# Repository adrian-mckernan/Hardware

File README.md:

# Hardware
PCB design files for LTC6946 based PLL array

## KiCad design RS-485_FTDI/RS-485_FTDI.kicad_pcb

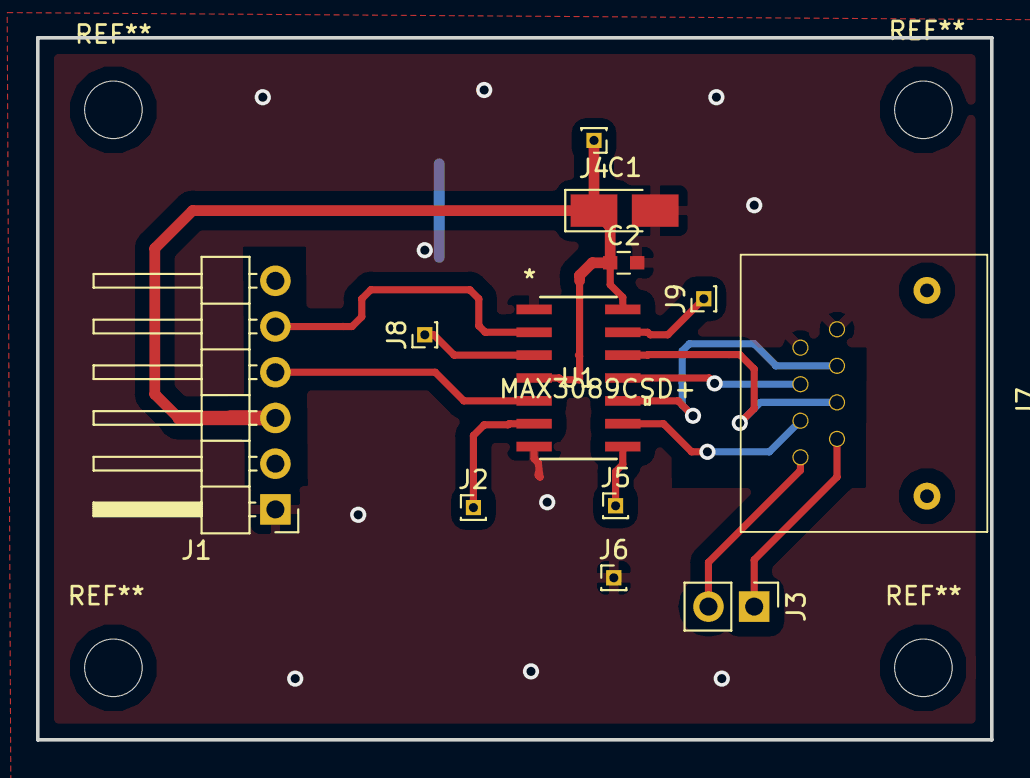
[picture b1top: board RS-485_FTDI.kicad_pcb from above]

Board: 2 copper layers, 53.0 x 39.0 mm, 12 parts (0 on the bottom side), 14 nets.

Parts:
C1: 10U; CP_Tantalum_Case-R_EIA-2012-12_Hand
C2: C; C_0603
J1: Conn_01x06; Pin_Header_Angled_1x06_Pitch2.54mm
J2, J4, J5, J6, J8, J9: Conn_01x01; Pin_Header_Straight_1x01_Pitch1.00mm
J3: Conn_01x02; Pin_Header_Straight_1x02_Pitch2.54mm
J7: RJ45; RJ-45_1572189
U1: MAX3089CSD+; MAX3089CSD&plus_

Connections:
+5V: C1.1, C2.1, J1.3, J4.1, U1.4, U1.14
GND: C1.2, C2.2, J1.1, J6.1, J7.1, J7.2, U1.1, U1.7
unnamed: J2.1, U1.6
unnamed: J3.1, J7.8
unnamed: J3.2, J7.7
unnamed: J5.1, U1.8
unnamed: J8.1, U1.3
unnamed: J9.1, U1.13
RXI: J1.5, U1.2
TXO: J1.4, U1.5
blue: J7.4, U1.12
orange: J7.6, U1.9
w_blue: J7.5, U1.11
w_orange: J7.3, U1.10

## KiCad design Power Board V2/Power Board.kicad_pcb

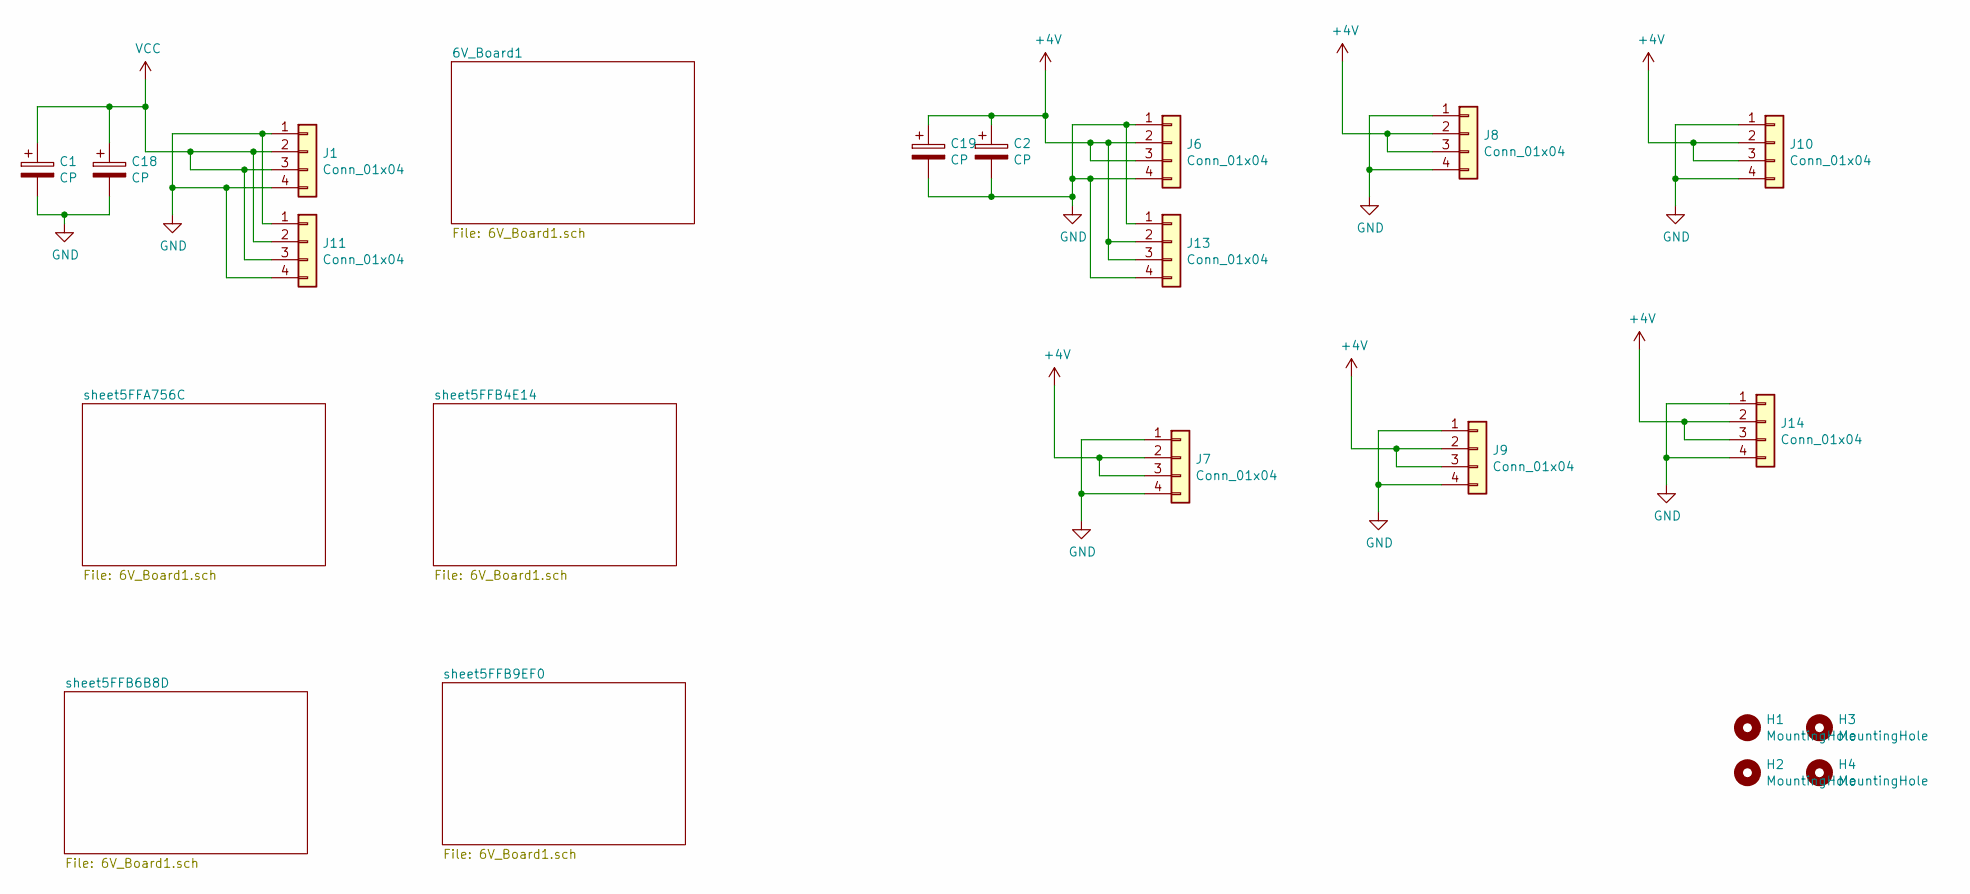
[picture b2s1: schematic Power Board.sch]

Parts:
C1, C2, C18, C19: CP; CP_Radial_D8.0mm_P3.50mm
H1, H2: MountingHole; MountingHole_3.2mm_M3
H3, H4: MountingHole; MountingHole_5.5mm
J1, J6, J7, J8, J9, J10, J11, J13, J14: Conn_01x04; Pin_Header_Straight_1x04_Pitch2.54mm

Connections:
+4V: C2.1, C19.1, J6.2, J6.3, J7.2, J7.3, J8.2, J8.3, J9.2, J9.3, J10.2, J10.3, J13.2, J13.3, J14.2, J14.3
GND: C1.2, C2.2, C18.2, C19.2, J1.1, J1.4, J6.1, J6.4, J7.1, J7.4, J8.1, J8.4, J9.1, J9.4, J10.1, J10.4, J11.1, J11.4, J13.1, J13.4, J14.1, J14.4; also elsewhere on the board
VCC: C1.1, C18.1, J1.2, J1.3, J11.2, J11.3; also elsewhere on the board

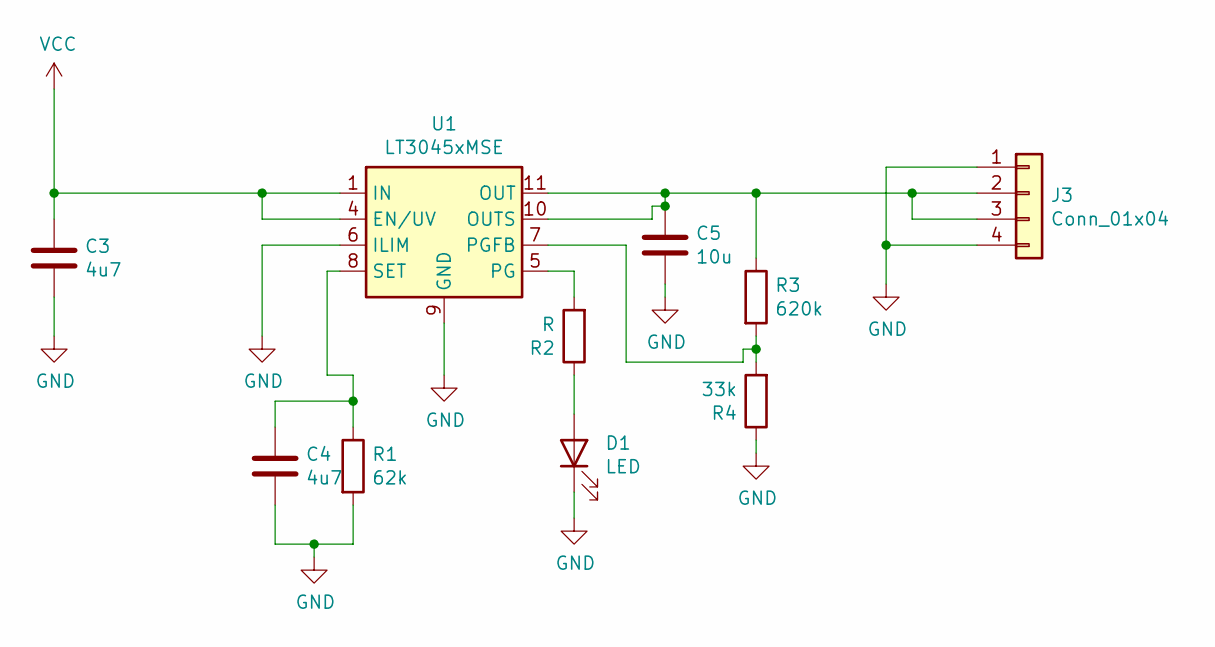
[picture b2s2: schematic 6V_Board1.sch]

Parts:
C3, C4: 4u7; C_0805_HandSoldering
C5: 10u; C_0805_HandSoldering
D1: LED; LED_D4.0mm
J3: Conn_01x04; Pin_Header_Straight_1x04_Pitch2.54mm
R1: 62k; R_0603_HandSoldering
R2: R; R_0603_HandSoldering
R3: 620k; R_0603_HandSoldering
R4: 33k; R_0603_HandSoldering
U1: LT3045xMSE; MSOP-12-1EP_3x4mm_P0.65mm_EP1.65x2.85mm

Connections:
GND: C3.2, C4.2, C5.2, D1.1 (K), J3.1, J3.4, R1.2, R4.1, U1.6 (ILIM), U1.9 (GND), U1.13 (GND); also elsewhere on the board
unnamed: C4.1, R1.1, U1.8 (SET)
unnamed: C5.1, J3.2, J3.3, R3.1, U1.10 (OUTS), U1.11 (OUT), U1.12 (OUT)
unnamed: D1.2 (A), R2.1
unnamed: R2.2, U1.5 (PG)
unnamed: R3.2, R4.2, U1.7 (PGFB)
VCC: C3.1, U1.1 (IN), U1.2 (IN), U1.3 (IN), U1.4 (EN/UV); also elsewhere on the board

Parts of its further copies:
C6, C7, C9, C10, C12, C13, C15, C16: 4u7; C_0805_HandSoldering
C8, C11, C14, C17: 10u; C_0805_HandSoldering
D2, D3, D4, D5: LED; LED_D4.0mm
J2, J4, J5, J12: Conn_01x04; Pin_Header_Straight_1x04_Pitch2.54mm
R6, R10, R14, R18: R; R_0603_HandSoldering
R7, R11, R15, R19: 620k; R_0603_HandSoldering
R8, R12, R16, R20: 33k; R_0603_HandSoldering
U2, U3, U4, U5: LT3045xMSE; MSOP-12-1EP_3x4mm_P0.65mm_EP1.65x2.85mm

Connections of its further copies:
GND: C6.2, C7.2, C8.2, C9.2, C10.2, C11.2, C12.2, C13.2, C14.2, C15.2, C16.2, C17.2, D2.1 (K), D3.1 (K), D4.1 (K), D5.1 (K), J2.1, J2.4, J4.1, J4.4, J5.1, J5.4, J12.1, J12.4, R8.1, R12.1, R16.1, R20.1, U2.6 (ILIM), U2.9 (GND), U2.13 (GND), U3.6 (ILIM), U3.9 (GND), U3.13 (GND), U4.6 (ILIM), U4.9 (GND), U4.13 (GND), U5.6 (ILIM), U5.9 (GND), U5.13 (GND); also elsewhere on the board
unnamed 4: C7.1, U2.8 (SET); also elsewhere on the board
unnamed: C8.1, J2.2, J2.3, R7.1, U2.10 (OUTS), U2.11 (OUT), U2.12 (OUT)
unnamed 6: C10.1, U3.8 (SET); also elsewhere on the board
unnamed: C11.1, J4.2, J4.3, R11.1, U3.10 (OUTS), U3.11 (OUT), U3.12 (OUT)
unnamed 8: C13.1, U4.8 (SET); also elsewhere on the board
unnamed: C14.1, J5.2, J5.3, R15.1, U4.10 (OUTS), U4.11 (OUT), U4.12 (OUT)
unnamed 10: C16.1, U5.8 (SET); also elsewhere on the board
unnamed: C17.1, J12.2, J12.3, R19.1, U5.10 (OUTS), U5.11 (OUT), U5.12 (OUT)
unnamed: D2.2 (A), R6.1
unnamed: D3.2 (A), R10.1
unnamed: D4.2 (A), R14.1
unnamed: D5.2 (A), R18.1
unnamed: R6.2, U2.5 (PG)
unnamed: R7.2, R8.2, U2.7 (PGFB)
unnamed: R10.2, U3.5 (PG)
unnamed: R11.2, R12.2, U3.7 (PGFB)
unnamed: R14.2, U4.5 (PG)
unnamed: R15.2, R16.2, U4.7 (PGFB)
unnamed: R18.2, U5.5 (PG)
unnamed: R19.2, R20.2, U5.7 (PGFB)
VCC: C6.1, C9.1, C12.1, C15.1, U2.1 (IN), U2.2 (IN), U2.3 (IN), U2.4 (EN/UV), U3.1 (IN), U3.2 (IN), U3.3 (IN), U3.4 (EN/UV), U4.1 (IN), U4.2 (IN), U4.3 (IN), U4.4 (EN/UV), U5.1 (IN), U5.2 (IN), U5.3 (IN), U5.4 (EN/UV); also elsewhere on the board

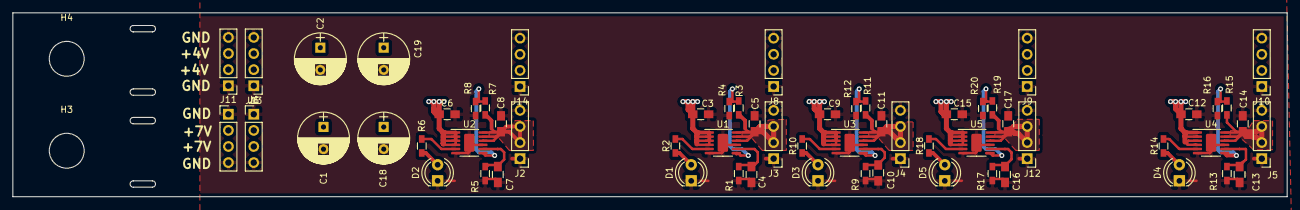
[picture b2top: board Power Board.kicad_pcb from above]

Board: 2 copper layers, 201.0 x 29.0 mm, 64 parts (0 on the bottom side), 28 nets.

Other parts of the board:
R5, R9, R13, R17: 62R; R_0603_HandSoldering

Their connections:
GND: R5.2, R9.2, R13.2, R17.2; also elsewhere on the board
unnamed 4: R5.1; also elsewhere on the board
unnamed 6: R9.1; also elsewhere on the board
unnamed 8: R13.1; also elsewhere on the board
unnamed 10: R17.1; also elsewhere on the board

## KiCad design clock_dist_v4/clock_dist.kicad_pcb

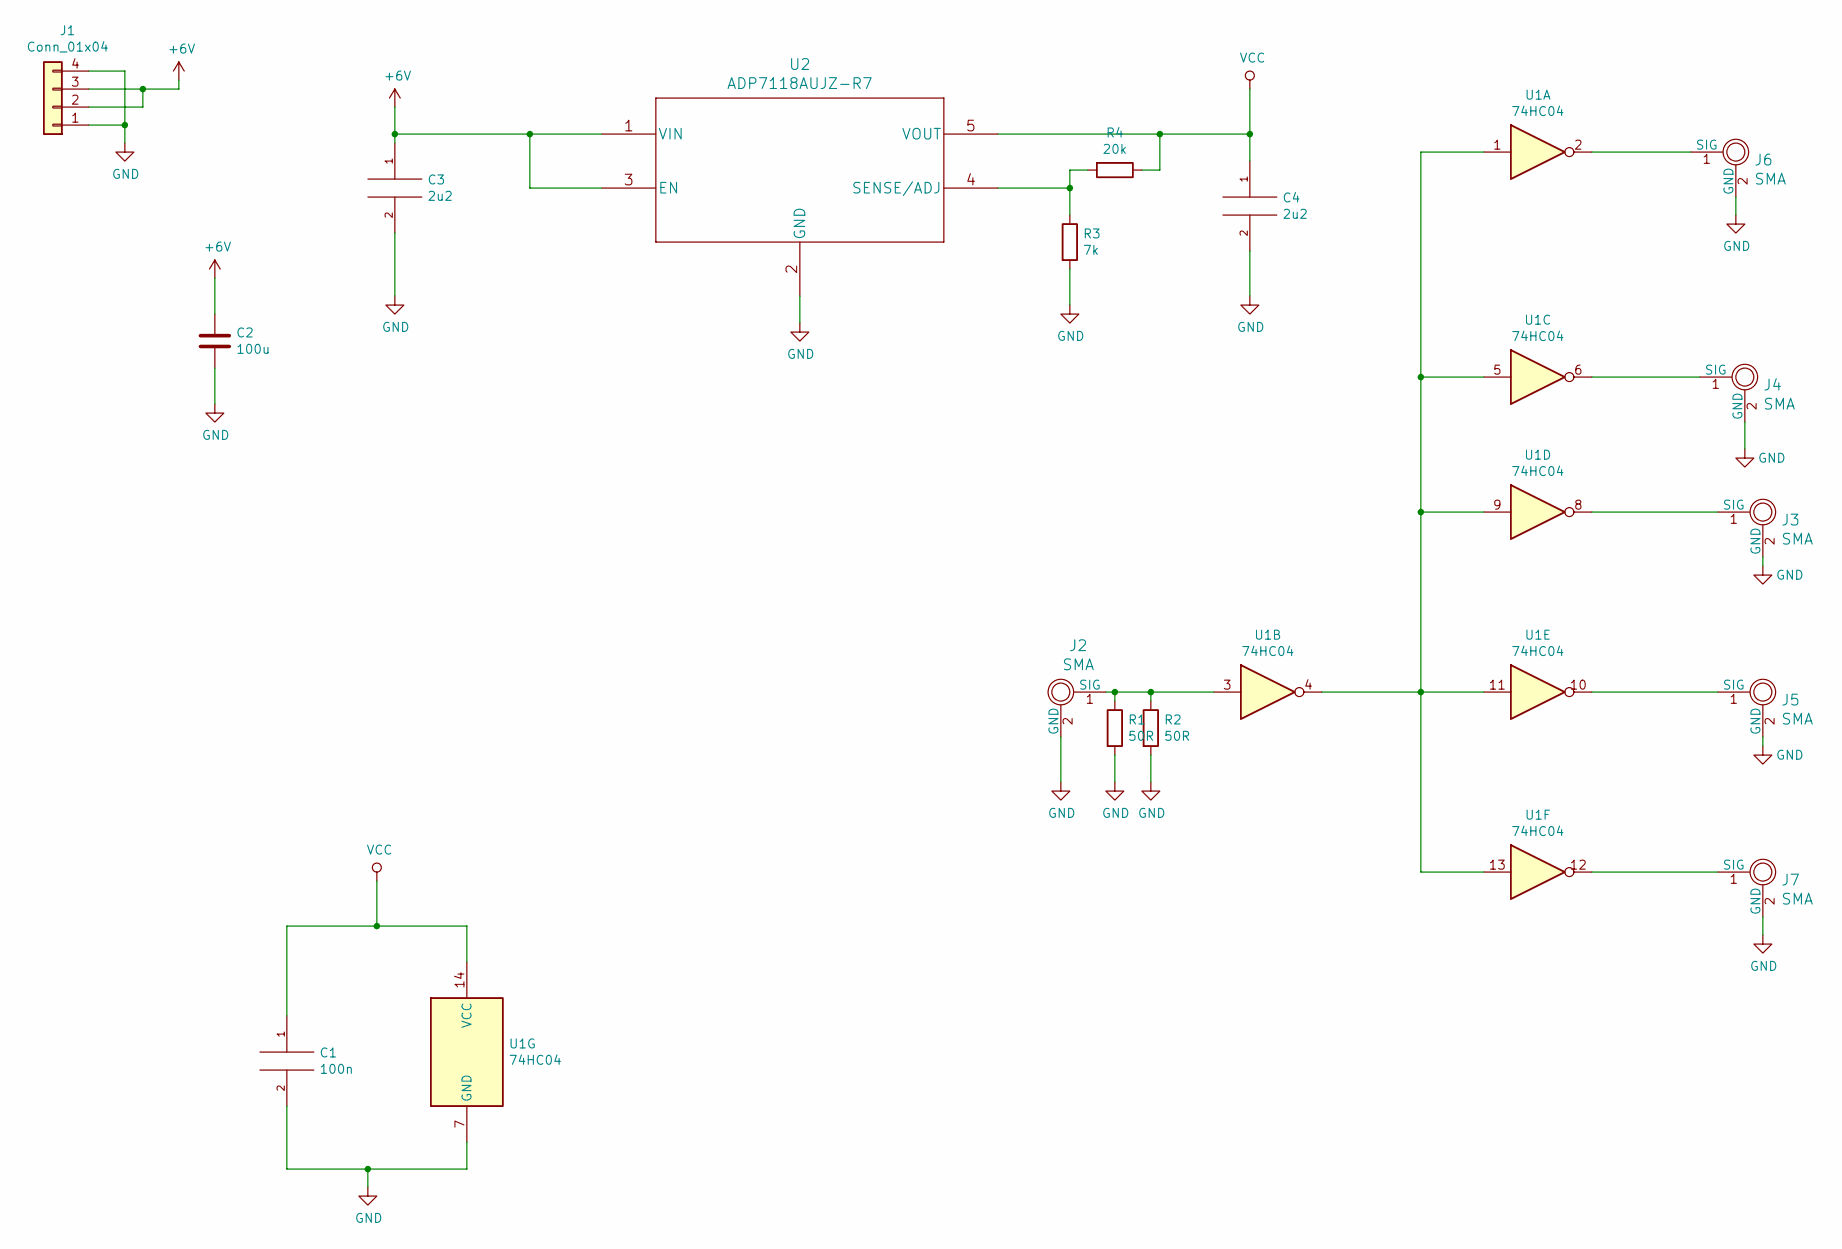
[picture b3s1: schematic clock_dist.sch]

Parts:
C1: 100n; C_0603_HandSoldering
C2: 100u; CP_Tantalum_Case-D_EIA-7343-31_Hand
C3, C4: 2u2; C_0603_1608Metric_Pad1.05x0.95mm_HandSolder
J1: Conn_01x04; Pin_Header_Angled_1x04_Pitch2.54mm
J2, J3, J4, J5, J6, J7: SMA; SMA_end_RS_170-6954
R1, R2: 50R; R_0603_HandSoldering
R3: 7k; R_0603_1608Metric_Pad1.05x0.95mm_HandSolder
R4: 20k; R_0603_1608Metric_Pad1.05x0.95mm_HandSolder
U1: 74HC04; SOIC-14_N
U2: ADP7118AUJZ-R7

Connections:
+6V: C2.1, C3.1, J1.2, J1.3, U2.1 (VIN), U2.3 (EN)
GND: C1.2, C2.2, C3.2, C4.2, J1.1, J1.4, J2.2 (GND), J3.2 (GND), J4.2 (GND), J5.2 (GND), J6.2 (GND), J7.2 (GND), R1.2, R2.2, R3.2, U1.7 (GND), U2.2 (GND)
unnamed: J2.1 (SIG), R1.1, R2.1, U1.3
unnamed: J3.1 (SIG), U1.8
unnamed: J4.1 (SIG), U1.6
unnamed: J5.1 (SIG), U1.10
unnamed: J6.1 (SIG), U1.2
unnamed: J7.1 (SIG), U1.12
unnamed: R3.1, R4.2, U2.4 (SENSE/ADJ)
unnamed: U1.1, U1.4, U1.5, U1.9, U1.11, U1.13
VCC: C1.1, C4.1, R4.1, U1.14 (VCC), U2.5 (VOUT)

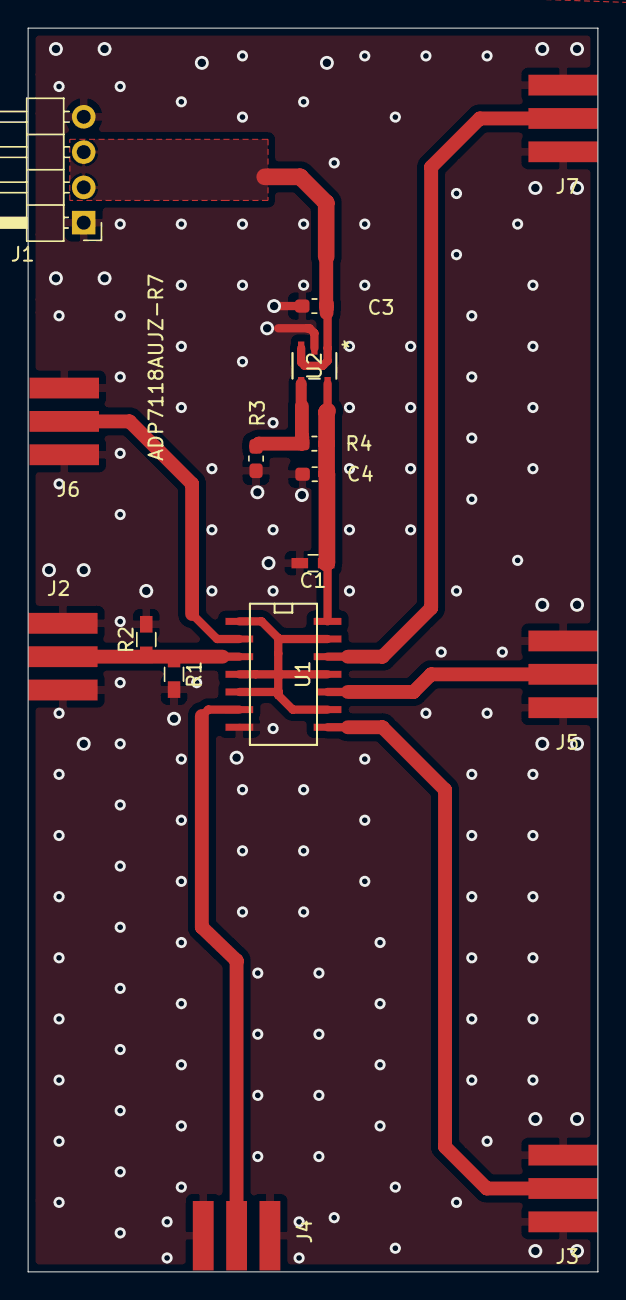
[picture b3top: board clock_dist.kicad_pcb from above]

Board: 2 copper layers, 41.0 x 89.5 mm, 16 parts (0 on the bottom side), 11 nets.

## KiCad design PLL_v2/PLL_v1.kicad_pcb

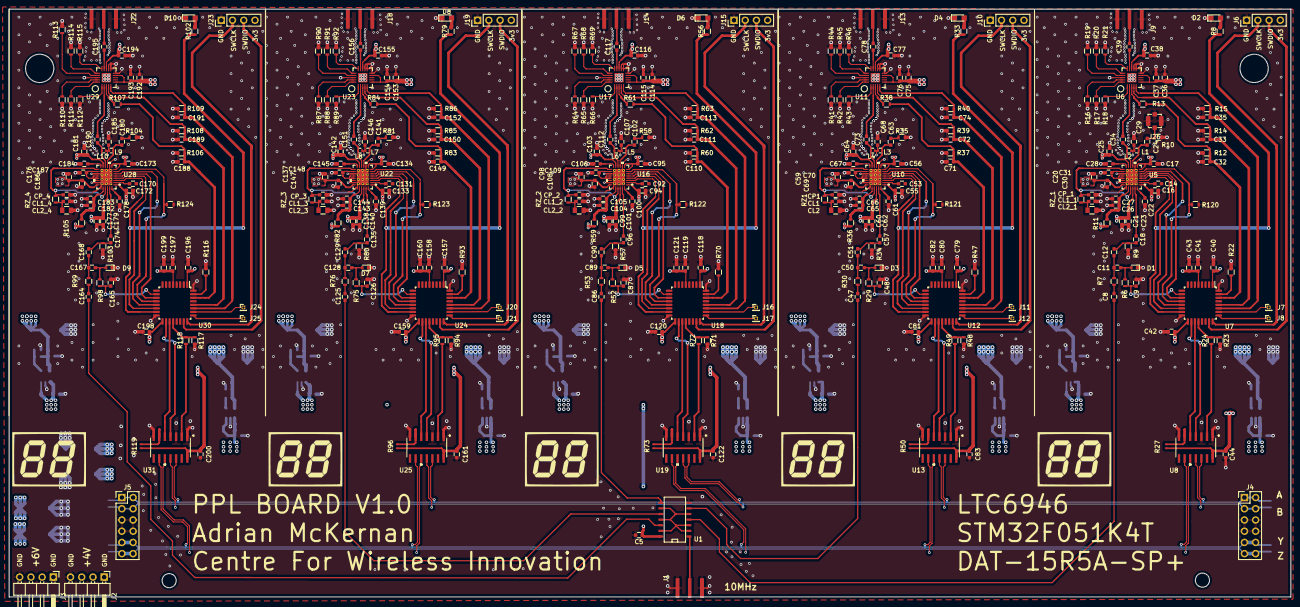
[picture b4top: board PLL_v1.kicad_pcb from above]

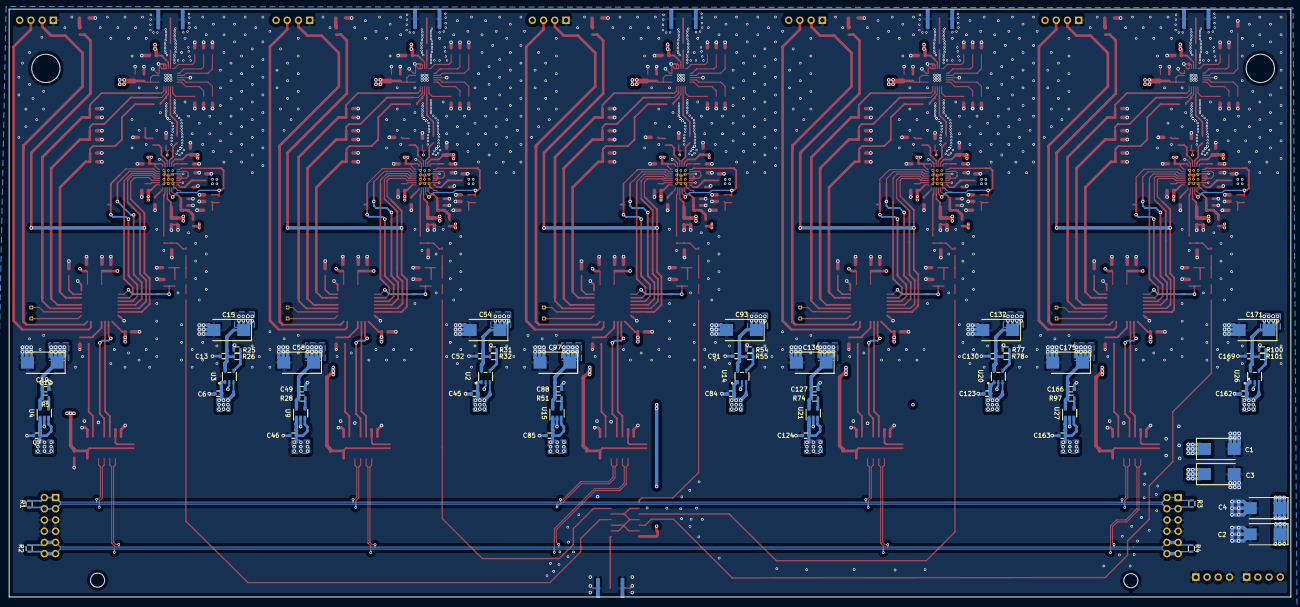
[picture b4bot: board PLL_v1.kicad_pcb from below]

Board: 4 copper layers, 290.0 x 133.0 mm, 425 parts (63 on the bottom side), 259 nets.

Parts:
C1, C2, C3, C4, C15, C19, C54, C58, C93, C97, C132, C136, C171, C175: 100u; CP_Tantalum_Case-D_EIA-7343-31_Wave
C5, C8, C12, C16, C17, C29, C36, C40, C41, C42, C43, C44, C47, C51, C55, C56, C68, C75, C79, C80, C81, C82, C83, C86, C90, C94, C95, C107, C114, C118, C119, C120, C121, C122, C125, C129, C133, C134, C146, C153, C157, C158, C159, C160, C161, C164, C168, C172, C173, C185, C192, C196, C197, C198, C199, C200: 100n; C_0603
C6, C13, C31, C45, C52, C70, C84, C91, C109, C123, C130, C148, C162, C169, C187: 2u2; C_0603
C7, C10, C18, C20, C21, C22, C26, C28, C46, C49, C57, C59, C60, C61, C65, C67, C85, C88, C96, C98, C99, C100, C104, C106, C124, C127, C135, C137, C138, C139, C143, C145, C163, C166, C174, C176, C177, C178, C182, C184: 1u; C_0603
C9, C48, C87, C126, C165: 10u; C_0603
C11, C50, C89, C128, C167: 47pF; C_0603
C14, C53, C92, C131, C170: 22n; C_0603
C23, C25, C27, C30, C62, C64, C66, C69, C101, C103, C105, C108, C140, C142, C144, C147, C179, C181, C183, C186: 10n; C_0603
C24, C32, C33, C34, C35, C37, C38, C39, C63, C71, C72, C73, C74, C76, C77, C78, C102, C110, C111, C112, C113, C115, C116, C117, C141, C149, C150, C151, C152, C154, C155, C156, C180, C188, C189, C190, C191, C193, C194, C195: 100p; C_0603
CL1, CL1_1, CL1_2, CL1_3, CL1_4: C; C_0603
CL2, CL2_1, CL2_2, CL2_3, CL2_4: C0805; C_0805
CP1: C; C_0603
CP_1, CP_2, CP_3, CP_4: C; C_0603
D1, D3, D5, D7, D9: BB202; D_SOD-523
D2, D4, D6, D8, D10: LED; LED_0805
H1, H2: MountingHole; MountingHole_6.4mm_M6
H3, H4: MountingHole; MountingHole_3.2mm_M3
J1, J9, J13, J14, J18, J22: SMA; CON-SMA-EDGE-S_RF_Sol
J2, J3: Conn_01x04; Pin_Header_Angled_1x04_Pitch2.54mm
J4, J5: Conn_02x06_Odd_Even; Pin_Header_Straight_2x06_Pitch2.54mm
J6, J10, J15, J19, J23: Conn_01x04; Pin_Header_Straight_1x04_Pitch2.54mm
J7, J8, J11, J12, J16, J17, J20, J21, J24, J25: Conn_01x01; Pin_Header_Straight_1x01_Pitch1.00mm
J26: Conn_Coaxial; Molex_Microcoaxial_RF
L1, L2, L3, L4, L5, L6, L7, L8, L9, L10: 68n; R_0402
R1, R2, R3, R4, R8, R33, R56, R79, R102: R; R_0603
R5, R6, R28, R29, R51, R52, R74, R75, R97, R98: 100k; R_0603
R7, R30, R53, R76, R99: 120R; R_0603
R9, R34, R57, R80, R103: 51.1R; R_0603
R10, R35, R58, R81, R104: 50R; R_0603
R11, R36, R59, R82, R105: 15R; R_0603
R12, R13, R14, R15, R16, R17, R18, R19, R20, R21, R37, R38, R39, R40, R41, R42, R43, R44, R45, R46, R60, R61, R62, R63, R64, R65, R66, R67, R68, R69, R83, R84, R85, R86, R87, R88, R89, R90, R91, R92, R106, R107, R108, R109, R110, R111, R112, R113, R114, R115: 10k; R_0603
R22, R47, R70, R93, R116: 47k; R_0603
R23, R48, R71, R94, R117: 3k3; R_0603
R24, R49, R72, R95, R118: 2k2; R_0603
R25, R31, R54, R77, R100: 19k6; R_0603
R26, R32, R55, R78, R101: 6k19; R_0603
R27, R50, R73, R96, R119: DNF; R_0402_NoSilk
R120, R121, R122, R123, R124: 200k; R_0603
RZ1: R; R_0603
RZ_1, RZ_2, RZ_3, RZ_4: R; R_0603
U1: 74HC04; SOIC-14_N
U2, U3, U14, U20, U26: ADP7118AUJZ-R7
U4, U9, U15, U21, U27: LDLN030; SOT-23-5
U5, U10, U16, U22, U28: LTC6946IUFD-4-PBF
U6, U11, U17, U23, U29: DAT-15R5A-SP+; minicircuits_DG983-2
U7, U12, U18, U24, U30: STM32F051K4Tx; LQFP-32_7x7mm_P0.8mm
U8, U13, U19, U25, U31: MAX3089; MAX3089CSD&plus_

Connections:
+4V: C1.1, C3.1, C7.1, C46.1, C85.1, C124.1, C163.1, J2.2, J2.3, U4.1, U4.3, U9.1, U9.3, U15.1, U15.3, U21.1, U21.3, U27.1, U27.3
+6V: C2.1, C4.1, C5.1, C6.1, C45.1, C84.1, C123.1, C162.1, J3.2, J3.3, U1.14, U2.1, U2.3, U3.1, U3.3, U14.1, U14.3, U20.1, U20.3, U26.1, U26.3
/10M_1: C8.2, U1.4
/10M_BUF: U1.2, U1.3, U1.5, U1.9, U1.11, U1.13
/10M_IN: J1.1, U1.1
/PLL_1/LTC6946_1/REF_in: C12.1, C18.2, R9.1
/PLL_1/LTC6946_1/RF_OUT: C39.1, J9.1
/PLL_1/LTC6946_1/SCLK: U5.5, U7.11
/PLL_1/LTC6946_1/SDI: U5.6, U7.13
/PLL_1/LTC6946_1/SDO: R120.1, U5.7, U7.12
/PLL_1/PLL1_3v3: C10.1, C16.1, C17.1, C19.1, C21.1, C23.1, C25.1, C29.2, C36.1, C37.1, C38.1, C40.1, C41.1, C42.1, C43.1, J6.4, L1.1, L2.2, R5.2, U4.5, U5.1, U5.8, U5.9, U5.13, U5.26, U6.6, U6.9, U6.13, U7.1, U7.5, U7.17
/PLL_1/PLL1_5v: C13.1, C15.1, C20.1, C30.2, C44.1, R11.1, R25.1, R27.2, U3.5, U5.22, U8.14
/PLL_1/STM32F051K4T_1/ANT_CLK: C33.1, R14.1, U6.4, U7.28
/PLL_1/STM32F051K4T_1/ANT_DATA: C32.1, R12.1, R13.2, U7.30
/PLL_1/STM32F051K4T_1/ANT_LE: C35.1, R15.1, U6.5, U7.27
/PLL_1/STM32F051K4T_1/PLL_STATE: R8.1, U5.3, U7.15
/PLL_1/STM32F051K4T_1/Phase_DAC: C9.2, R6.2, U7.10
/PLL_1/STM32F051K4T_1/SPI_~CS: U5.4, U7.14
/PLL_1/STM32F051K4T_1/STM_RX: R23.1, R24.2, U7.20
/PLL_1/STM32F051K4T_1/STM_TX: U7.19, U8.5
/PLL_1/STM32F051K4T_1/SWCLK_1: J6.2, U7.24
/PLL_1/STM32F051K4T_1/SWDIO_1: J6.3, U7.23
/PLL_1/STM32F051K4T_1/TX_EN: U7.18, U8.4
/PLL_2/10MHz: C47.2, U1.6
/PLL_2/LTC6946_1/REF_in: C51.1, C57.2, R34.1
/PLL_2/LTC6946_1/RF_OUT: C78.1, J13.1
/PLL_2/LTC6946_1/SCLK: U10.5, U12.11
/PLL_2/LTC6946_1/SDI: U10.6, U12.13
/PLL_2/LTC6946_1/SDO: R121.1, U10.7, U12.12
/PLL_2/PLL1_3v3: C49.1, C55.1, C56.1, C58.1, C60.1, C62.1, C64.1, C68.2, C75.1, C76.1, C77.1, C79.1, C80.1, C81.1, C82.1, J10.4, L3.1, L4.2, R28.2, U9.5, U10.1, U10.8, U10.9, U10.13, U10.26, U11.6, U11.9, U11.13, U12.1, U12.5, U12.17
/PLL_2/PLL1_5v: C52.1, C54.1, C59.1, C69.2, C83.1, R31.1, R36.1, R50.2, U2.5, U10.22, U13.14
/PLL_2/STM32F051K4T_1/ANT_CLK: C72.1, R39.1, U11.4, U12.28
/PLL_2/STM32F051K4T_1/ANT_DATA: C71.1, R37.1, R38.2, U12.30
/PLL_2/STM32F051K4T_1/ANT_LE: C74.1, R40.1, U11.5, U12.27
/PLL_2/STM32F051K4T_1/PLL_STATE: R33.1, U10.3, U12.15
/PLL_2/STM32F051K4T_1/Phase_DAC: C48.2, R29.2, U12.10
/PLL_2/STM32F051K4T_1/SPI_~CS: U10.4, U12.14
/PLL_2/STM32F051K4T_1/STM_RX: R48.1, R49.2, U12.20
/PLL_2/STM32F051K4T_1/STM_TX: U12.19, U13.5
/PLL_2/STM32F051K4T_1/SWCLK_1: J10.2, U12.24
/PLL_2/STM32F051K4T_1/SWDIO_1: J10.3, U12.23
/PLL_2/STM32F051K4T_1/TX_EN: U12.18, U13.4
/PLL_3/10MHz: C86.2, U1.8
/PLL_3/LTC6946_1/REF_in: C90.1, C96.2, R57.1
/PLL_3/LTC6946_1/RF_OUT: C117.1, J14.1
/PLL_3/LTC6946_1/SCLK: U16.5, U18.11
/PLL_3/LTC6946_1/SDI: U16.6, U18.13
/PLL_3/LTC6946_1/SDO: R122.1, U16.7, U18.12
/PLL_3/PLL1_3v3: C88.1, C94.1, C95.1, C97.1, C99.1, C101.1, C103.1, C107.2, C114.1, C115.1, C116.1, C118.1, C119.1, C120.1, C121.1, J15.4, L5.1, L6.2, R51.2, U15.5, U16.1, U16.8, U16.9, U16.13, U16.26, U17.6, U17.9, U17.13, U18.1, U18.5, U18.17
/PLL_3/PLL1_5v: C91.1, C93.1, C98.1, C108.2, C122.1, R54.1, R59.1, R73.2, U14.5, U16.22, U19.14
/PLL_3/STM32F051K4T_1/ANT_CLK: C111.1, R62.1, U17.4, U18.28
/PLL_3/STM32F051K4T_1/ANT_DATA: C110.1, R60.1, R61.2, U18.30
/PLL_3/STM32F051K4T_1/ANT_LE: C113.1, R63.1, U17.5, U18.27
/PLL_3/STM32F051K4T_1/PLL_STATE: R56.1, U16.3, U18.15
/PLL_3/STM32F051K4T_1/Phase_DAC: C87.2, R52.2, U18.10
/PLL_3/STM32F051K4T_1/SPI_~CS: U16.4, U18.14
/PLL_3/STM32F051K4T_1/STM_RX: R71.1, R72.2, U18.20
/PLL_3/STM32F051K4T_1/STM_TX: U18.19, U19.5
/PLL_3/STM32F051K4T_1/SWCLK_1: J15.2, U18.24
/PLL_3/STM32F051K4T_1/SWDIO_1: J15.3, U18.23
/PLL_3/STM32F051K4T_1/TX_EN: U18.18, U19.4
/PLL_4/10MHz: C125.2, U1.10
/PLL_4/LTC6946_1/REF_in: C129.1, C135.2, R80.1
/PLL_4/LTC6946_1/RF_OUT: C156.1, J18.1
/PLL_4/LTC6946_1/SCLK: U22.5, U24.11
/PLL_4/LTC6946_1/SDI: U22.6, U24.13
/PLL_4/LTC6946_1/SDO: R123.1, U22.7, U24.12
/PLL_4/PLL1_3v3: C127.1, C133.1, C134.1, C136.1, C138.1, C140.1, C142.1, C146.2, C153.1, C154.1, C155.1, C157.1, C158.1, C159.1, C160.1, J19.4, L7.1, L8.2, R74.2, U21.5, U22.1, U22.8, U22.9, U22.13, U22.26, U23.6, U23.9, U23.13, U24.1, U24.5, U24.17
/PLL_4/PLL1_5v: C130.1, C132.1, C137.1, C147.2, C161.1, R77.1, R82.1, R96.2, U20.5, U22.22, U25.14
/PLL_4/STM32F051K4T_1/ANT_CLK: C150.1, R85.1, U23.4, U24.28
/PLL_4/STM32F051K4T_1/ANT_DATA: C149.1, R83.1, R84.2, U24.30
/PLL_4/STM32F051K4T_1/ANT_LE: C152.1, R86.1, U23.5, U24.27
/PLL_4/STM32F051K4T_1/PLL_STATE: R79.1, U22.3, U24.15
/PLL_4/STM32F051K4T_1/Phase_DAC: C126.2, R75.2, U24.10
/PLL_4/STM32F051K4T_1/SPI_~CS: U22.4, U24.14
/PLL_4/STM32F051K4T_1/STM_RX: R94.1, R95.2, U24.20
/PLL_4/STM32F051K4T_1/STM_TX: U24.19, U25.5
/PLL_4/STM32F051K4T_1/SWCLK_1: J19.2, U24.24
/PLL_4/STM32F051K4T_1/SWDIO_1: J19.3, U24.23
/PLL_4/STM32F051K4T_1/TX_EN: U24.18, U25.4
/PLL_5/10MHz: C164.2, U1.12
/PLL_5/LTC6946_1/REF_in: C168.1, C174.2, R103.1
/PLL_5/LTC6946_1/RF_OUT: C195.1, J22.1
/PLL_5/LTC6946_1/SCLK: U28.5, U30.11
/PLL_5/LTC6946_1/SDI: U28.6, U30.13
/PLL_5/LTC6946_1/SDO: R124.1, U28.7, U30.12
/PLL_5/PLL1_3v3: C166.1, C172.1, C173.1, C175.1, C177.1, C179.1, C181.1, C185.2, C192.1, C193.1, C194.1, C196.1, C197.1, C198.1, C199.1, J23.4, L9.1, L10.2, R97.2, U27.5, U28.1, U28.8, U28.9, U28.13, U28.26, U29.6, U29.9, U29.13, U30.1, U30.5, U30.17
/PLL_5/PLL1_5v: C169.1, C171.1, C176.1, C186.2, C200.1, R100.1, R105.1, R119.2, U26.5, U28.22, U31.14
/PLL_5/STM32F051K4T_1/ANT_CLK: C189.1, R108.1, U29.4, U30.28
/PLL_5/STM32F051K4T_1/ANT_DATA: C188.1, R106.1, R107.2, U30.30
/PLL_5/STM32F051K4T_1/ANT_LE: C191.1, R109.1, U29.5, U30.27
/PLL_5/STM32F051K4T_1/PLL_STATE: R102.1, U28.3, U30.15
/PLL_5/STM32F051K4T_1/Phase_DAC: C165.2, R98.2, U30.10
/PLL_5/STM32F051K4T_1/SPI_~CS: U28.4, U30.14
/PLL_5/STM32F051K4T_1/STM_RX: R117.1, R118.2, U30.20
/PLL_5/STM32F051K4T_1/STM_TX: U30.19, U31.5
/PLL_5/STM32F051K4T_1/SWCLK_1: J23.2, U30.24
/PLL_5/STM32F051K4T_1/SWDIO_1: J23.3, U30.23
/PLL_5/STM32F051K4T_1/TX_EN: U30.18, U31.4
GND: C1.2, C2.2, C3.2, C4.2, C5.2, C6.2, C7.2, C9.1, C10.2, C13.2, C15.2, C16.2, C17.2, C19.2, C20.2, C21.2, C22.2, C23.2, C25.2, C26.1, C27.1, C28.2, C29.1, C30.1, C31.1, C32.2, C33.2, C35.2, C36.2, C37.2, C38.2, C40.2, C41.2, C42.2, C43.2, C44.2, C45.2, C46.2, C48.1, C49.2, C52.2, C54.2, C55.2, C56.2, C58.2, C59.2, C60.2, C61.2, C62.2, C64.2, C65.1, C66.1, C67.2, C68.1, C69.1, C70.1, C71.2, C72.2, C74.2, C75.2, C76.2, C77.2, C79.2, C80.2, C81.2, C82.2, C83.2, C84.2, C85.2, C87.1, C88.2, C91.2, C93.2, C94.2, C95.2, C97.2, C98.2, C99.2, C100.2, C101.2, C103.2, C104.1, C105.1, C106.2, C107.1, C108.1, C109.1, C110.2, C111.2, C113.2, C114.2, C115.2, C116.2, C118.2, C119.2, C120.2, C121.2, C122.2, C123.2, C124.2, C126.1, C127.2, C130.2, C132.2, C133.2, C134.2, C136.2, C137.2, C138.2, C139.2, C140.2, C142.2, C143.1, C144.1, C145.2, C146.1, C147.1, C148.1, C149.2, C150.2, C152.2, C153.2, C154.2, C155.2, C157.2, C158.2, C159.2, C160.2, C161.2, C162.2, C163.2, C165.1, C166.2, C169.2, C171.2, C172.2, C173.2, C175.2, C176.2, C177.2, C178.2, C179.2, C181.2, C182.1, C183.1, C184.2, C185.1, C186.1, C187.1, C188.2, C189.2, C191.2, C192.2, C193.2, C194.2, C196.2, C197.2, C198.2, C199.2, C200.2, CL1.2, CL1_1.2, CL1_2.2, CL1_3.2, CL1_4.2, CL2.2, CL2_1.2, CL2_2.2, CL2_3.2, CL2_4.2, CP1.2, CP_1.2, CP_2.2, CP_3.2, CP_4.2, D1.1, D2.1, D3.1, D4.1, D5.1, D6.1, D7.1, D8.1, D9.1, D10.1, J1.2, J2.1, J2.4, J3.1, J3.4, J4.5, J4.6, J4.7, J4.8, J5.5, J5.6, J5.7, J5.8, J6.1, J9.2, J10.1, J13.2, J14.2, J15.1, J18.2, J19.1, J22.2, J23.1, J26.2, R9.2, R10.2, R12.2, R14.2, R15.2, R16.2, R17.2, R18.2, R19.1, R20.1, R21.1, R22.2, R23.2, R26.2, R32.2, R34.2, R35.2, R37.2, R39.2, R40.2, R41.2, R42.2, R43.2, R44.1, R45.1, R46.1, R47.2, R48.2, R55.2, R57.2, R58.2, R60.2, R62.2, R63.2, R64.2, R65.2, R66.2, R67.1, R68.1, R69.1, R70.2, R71.2, R78.2, R80.2, R81.2, R83.2, R85.2, R86.2, R87.2, R88.2, R89.2, R90.1, R91.1, R92.1, R93.2, R94.2, R101.2, R103.2, R104.2, R106.2, R108.2, R109.2, R110.2, R111.2, R112.2, R113.1, R114.1, R115.1, R116.2, R117.2, R120.2, R121.2, R122.2, R123.2, R124.2, U1.7, U2.2, U3.2, U4.2, U5.10, U5.17, U5.21, U5.23, U5.29, U6.10, U6.11, U6.12, U6.18, U6.21, U7.16, U7.32, U8.1, U8.3, U8.7, U9.2, U10.10, U10.17, U10.21, U10.23, U10.29, U11.10, U11.11, U11.12, U11.18, U11.21, U12.16, U12.32, U13.1, U13.3, U13.7, U14.2, U15.2, U16.10, U16.17, U16.21, U16.23, U16.29, U17.10, U17.11, U17.12, U17.18, U17.21, U18.16, U18.32, U19.1, U19.3, U19.7, U20.2, U21.2, U22.10, U22.17, U22.21, U22.23, U22.29, U23.10, U23.11, U23.12, U23.18, U23.21, U24.16, U24.32, U25.1, U25.3, U25.7, U26.2, U27.2, U28.10, U28.17, U28.21, U28.23, U28.29, U29.10, U29.11, U29.12, U29.18, U29.21, U30.16, U30.32, U31.1, U31.3, U31.7
unnamed: C8.1, R7.2
unnamed: C11.1, D1.2, R6.1
unnamed: C11.2, C12.2, R7.1
unnamed: C14.1, U5.2
unnamed: C18.1, U5.27
unnamed: C22.1, U5.28
unnamed: C24.1, L1.2, U5.11
unnamed: C24.2, J26.1, R10.1
unnamed: C26.2, C27.2, R11.2, U5.24
unnamed: C28.1, U5.14
unnamed: C31.2, U5.16, U5.18, U5.19, U5.20
unnamed: C34.1, U6.2
unnamed: C34.2, L2.1, U5.12
unnamed: C39.2, U6.14
unnamed: C47.1, R30.2
unnamed: C50.1, D3.2, R29.1
unnamed: C50.2, C51.2, R30.1
unnamed: C53.1, U10.2
unnamed: C57.1, U10.27
unnamed: C61.1, U10.28
unnamed: C63.1, L3.2, U10.11
unnamed: C63.2, R35.1
unnamed: C65.2, C66.2, R36.2, U10.24
unnamed: C67.1, U10.14
unnamed: C70.2, U10.16, U10.18, U10.19, U10.20
unnamed: C73.1, U11.2
unnamed: C73.2, L4.1, U10.12
unnamed: C78.2, U11.14
unnamed: C86.1, R53.2
unnamed: C89.1, D5.2, R52.1
unnamed: C89.2, C90.2, R53.1
unnamed: C92.1, U16.2
unnamed: C96.1, U16.27
unnamed: C100.1, U16.28
unnamed: C102.1, L5.2, U16.11
unnamed: C102.2, R58.1
unnamed: C104.2, C105.2, R59.2, U16.24
unnamed: C106.1, U16.14
unnamed: C109.2, U16.16, U16.18, U16.19, U16.20
unnamed: C112.1, U17.2
unnamed: C112.2, L6.1, U16.12
unnamed: C117.2, U17.14
unnamed: C125.1, R76.2
unnamed: C128.1, D7.2, R75.1
unnamed: C128.2, C129.2, R76.1
unnamed: C131.1, U22.2
unnamed: C135.1, U22.27
unnamed: C139.1, U22.28
unnamed: C141.1, L7.2, U22.11
unnamed: C141.2, R81.1
unnamed: C143.2, C144.2, R82.2, U22.24
unnamed: C145.1, U22.14
unnamed: C148.2, U22.16, U22.18, U22.19, U22.20
unnamed: C151.1, U23.2
unnamed: C151.2, L8.1, U22.12
unnamed: C156.2, U23.14
unnamed: C164.1, R99.2
unnamed: C167.1, D9.2, R98.1
unnamed: C167.2, C168.2, R99.1
unnamed: C170.1, U28.2
unnamed: C174.1, U28.27
unnamed: C178.1, U28.28
unnamed: C180.1, L9.2, U28.11
unnamed: C180.2, R104.1
unnamed: C182.2, C183.2, R105.2, U28.24
unnamed: C184.1, U28.14
unnamed: C187.2, U28.16, U28.18, U28.19, U28.20
unnamed: C190.1, U29.2
unnamed: C190.2, L10.1, U28.12
unnamed: C195.2, U29.14
unnamed: CL1.1, CL2.1, RZ1.2
unnamed: CL1_1.1, CL2_1.1, RZ_1.2
unnamed: CL1_2.1, CL2_2.1, RZ_2.2
unnamed: CL1_3.1, CL2_3.1, RZ_3.2
unnamed: CL1_4.1, CL2_4.1, RZ_4.2
unnamed: CP1.1, RZ1.1, U10.15, U10.25
unnamed: CP_1.1, RZ_1.1, U5.15, U5.25
unnamed: CP_2.1, RZ_2.1, U16.15, U16.25
unnamed: CP_3.1, RZ_3.1, U22.15, U22.25
unnamed: CP_4.1, RZ_4.1, U28.15, U28.25
unnamed: D2.2, R8.2
unnamed: D4.2, R33.2
unnamed: D6.2, R56.2
unnamed: D8.2, R79.2
unnamed: D10.2, R102.2
unnamed: J7.1, U7.26
unnamed: J8.1, U7.25
unnamed: J11.1, U12.26
unnamed: J12.1, U12.25
unnamed: J16.1, U18.26
unnamed: J17.1, U18.25
unnamed: J20.1, U24.26
unnamed: J21.1, U24.25
unnamed: J24.1, U30.26
unnamed: J25.1, U30.25
unnamed: R5.1, U4.4
unnamed: R13.1, U6.3
unnamed: R16.1, U6.19
unnamed: R17.1, U6.20
unnamed: R18.1, U6.1
unnamed: R19.2, U6.17
unnamed: R20.2, U6.16
unnamed: R21.2, U6.15
unnamed: R22.1, U7.31
unnamed: R24.1, U8.2
unnamed: R25.2, R26.1, U3.4
unnamed: R27.1, U8.6
unnamed: R28.1, U9.4
unnamed: R31.2, R32.1, U2.4
unnamed: R38.1, U11.3
unnamed: R41.1, U11.19
unnamed: R42.1, U11.20
unnamed: R43.1, U11.1
unnamed: R44.2, U11.17
unnamed: R45.2, U11.16
unnamed: R46.2, U11.15
unnamed: R47.1, U12.31
unnamed: R49.1, U13.2
unnamed: R50.1, U13.6
unnamed: R51.1, U15.4
unnamed: R54.2, R55.1, U14.4
unnamed: R61.1, U17.3
unnamed: R64.1, U17.19
unnamed: R65.1, U17.20
unnamed: R66.1, U17.1
unnamed: R67.2, U17.17
unnamed: R68.2, U17.16
unnamed: R69.2, U17.15
unnamed: R70.1, U18.31
unnamed: R72.1, U19.2
unnamed: R73.1, U19.6
unnamed: R74.1, U21.4
unnamed: R77.2, R78.1, U20.4
unnamed: R84.1, U23.3
unnamed: R87.1, U23.19
unnamed: R88.1, U23.20
unnamed: R89.1, U23.1
unnamed: R90.2, U23.17
unnamed: R91.2, U23.16
unnamed: R92.2, U23.15
unnamed: R93.1, U24.31
unnamed: R95.1, U25.2
unnamed: R96.1, U25.6
unnamed: R97.1, U27.4
unnamed: R100.2, R101.1, U26.4
unnamed: R107.1, U29.3
unnamed: R110.1, U29.19
unnamed: R111.1, U29.20
unnamed: R112.1, U29.1
unnamed: R113.2, U29.17
unnamed: R114.2, U29.16
unnamed: R115.2, U29.15
unnamed: R116.1, U30.31
unnamed: R118.1, U31.2
unnamed: R119.1, U31.6
RCV+: J4.1, J4.2, J5.1, J5.2, R1.2, R3.2, U8.12, U13.12, U19.12, U25.12, U31.12
RCV-: J4.3, J4.4, J5.3, J5.4, R1.1, R3.1, U8.11, U13.11, U19.11, U25.11, U31.11
TX+: J4.9, J4.10, J5.9, J5.10, R2.1, R4.1, U8.9, U13.9, U19.9, U25.9, U31.9
TX-: J4.11, J4.12, J5.11, J5.12, R2.2, R4.2, U8.10, U13.10, U19.10, U25.10, U31.10

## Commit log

2022-02-10 Add clock distribution board
2022-02-10 Add PLL board
2022-02-10 Add Power board
2022-02-10 Add RS-485 breakout
2022-02-10 Add RS-485 to FTDI board

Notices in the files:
parts and their libraries:
Copyright 2016 Accelerated Designs. All rights reserved.
